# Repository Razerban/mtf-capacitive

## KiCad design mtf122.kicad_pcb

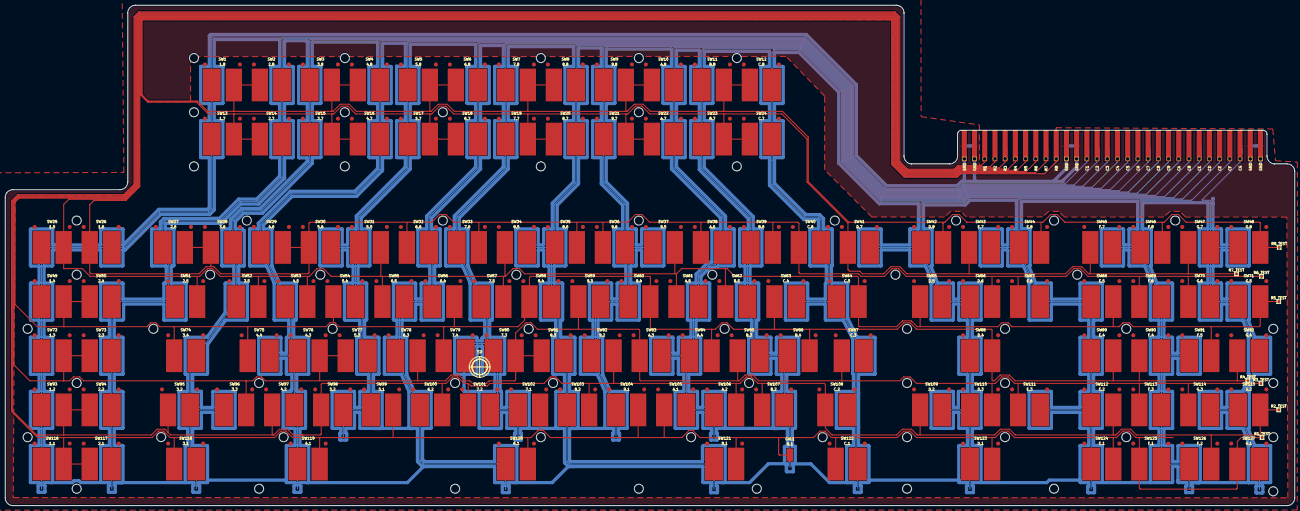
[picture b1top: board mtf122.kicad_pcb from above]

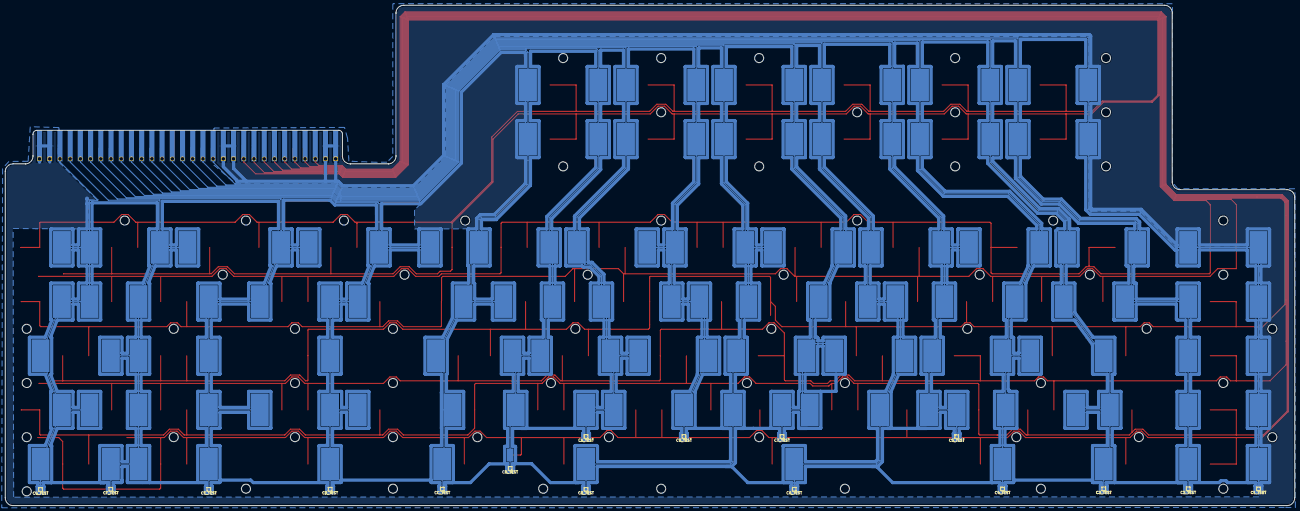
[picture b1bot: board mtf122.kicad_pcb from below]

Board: 2 copper layers, 500.0 x 194.0 mm, 153 parts (16 on the bottom side), 25 nets.

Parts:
C1_TEST, C2_TEST, C3_TEST, C4_TEST, C5_TEST, C6_TEST, C7_TEST, C8_TEST, C9_TEST: TestPoint_Pad_1.0x1.0mm
CAL1: B,1; CAL_CAP_IBM_F
CA_TEST: TestPoint_Pad_1.0x1.0mm
CB_TEST: TestPoint_Pad_1.0x1.0mm
CC_TEST: TestPoint_Pad_1.0x1.0mm
CD_TEST: TestPoint_Pad_1.0x1.0mm
CE_TEST: TestPoint_Pad_1.0x1.0mm
CF_TEST: TestPoint_Pad_1.0x1.0mm
CG_TEST: TestPoint_Pad_1.0x1.0mm
J1: CONN_CAP_IBM_F
R1_TEST, R2_TEST, R3_TEST, R4_TEST, R5_TEST, R6_TEST, R7_TEST, R8_TEST: TestPoint_Pad_1.0x1.0mm
SW1: 1,8; SW_CAP_IBM_F_ALT
SW2: 2,8; SW_CAP_IBM_F
SW3: 3,8; SW_CAP_IBM_F_ALT
SW4: 4,8; SW_CAP_IBM_F
SW5: 5,8; SW_CAP_IBM_F_ALT
SW6: 6,8; SW_CAP_IBM_F
SW7: 7,8; SW_CAP_IBM_F_ALT
SW8: 8,8; SW_CAP_IBM_F
SW9: 9,8; SW_CAP_IBM_F_ALT
SW10: A,8; SW_CAP_IBM_F
SW11: B,8; SW_CAP_IBM_F_ALT
SW12: C,8; SW_CAP_IBM_F
SW13: 1,7; SW_CAP_IBM_F_ALT
SW14: 2,7; SW_CAP_IBM_F
SW15: 3,7; SW_CAP_IBM_F_ALT
SW16: 4,7; SW_CAP_IBM_F
SW17: 5,7; SW_CAP_IBM_F_ALT
SW18: 6,7; SW_CAP_IBM_F
SW19: 7,7; SW_CAP_IBM_F_ALT
SW20: 8,7; SW_CAP_IBM_F
SW21: 9,7; SW_CAP_IBM_F_ALT
SW22: A,7; SW_CAP_IBM_F
SW23: B,7; SW_CAP_IBM_F_ALT
SW24: C,7; SW_CAP_IBM_F
SW25: 1,5; SW_CAP_IBM_F_ALT
SW26: 1,6; SW_CAP_IBM_F
SW27: 2,6; SW_CAP_IBM_F_ALT
SW28: 3,6; SW_CAP_IBM_F
SW29: 4,6; SW_CAP_IBM_F_ALT
SW30: 5,6; SW_CAP_IBM_F
SW31: 5,5; SW_CAP_IBM_F_ALT
SW32: 6,6; SW_CAP_IBM_F
SW33: 7,6; SW_CAP_IBM_F_ALT
SW34: 8,5; SW_CAP_IBM_F
SW35: 8,6; SW_CAP_IBM_F_ALT
SW36: 9,6; SW_CAP_IBM_F
SW37: 9,5; SW_CAP_IBM_F_ALT
SW38: A,6; SW_CAP_IBM_F
SW39: B,6; SW_CAP_IBM_F_ALT
SW40: C,6; SW_CAP_IBM_F
SW41: D,7; SW_CAP_IBM_F
SW42: D,8; SW_CAP_IBM_F_ALT
SW43: E,7; SW_CAP_IBM_F
SW44: E,8; SW_CAP_IBM_F_ALT
SW45: F,7; SW_CAP_IBM_F
SW46: F,8; SW_CAP_IBM_F_ALT
SW47: G,7; SW_CAP_IBM_F
SW48: G,8; SW_CAP_IBM_F_ALT
SW49: 1,4; SW_CAP_IBM_F_ALT
SW50: 2,4; SW_CAP_IBM_F
SW51: 2,5; SW_CAP_IBM_F_ALT
SW52: 3,5; SW_CAP_IBM_F_ALT
SW53: 4,5; SW_CAP_IBM_F_ALT
SW54: 5,4; SW_CAP_IBM_F
SW55: 6,5; SW_CAP_IBM_F
SW56: 6,4; SW_CAP_IBM_F_ALT
SW57: 7,5; SW_CAP_IBM_F_ALT
SW58: 8,4; SW_CAP_IBM_F
SW59: 9,3; SW_CAP_IBM_F
SW60: 9,4; SW_CAP_IBM_F_ALT
SW61: A,5; SW_CAP_IBM_F
SW62: B,5; SW_CAP_IBM_F
SW63: C,4; SW_CAP_IBM_F
SW64: C,5; SW_CAP_IBM_F_ALT
SW65: D,5; SW_CAP_IBM_F
SW66: D,6; SW_CAP_IBM_F_ALT
SW67: E,6; SW_CAP_IBM_F
SW68: E,5; SW_CAP_IBM_F_ALT
SW69: F,6; SW_CAP_IBM_F
SW70: G,6; SW_CAP_IBM_F
SW71: G,5; SW_CAP_IBM_F_ALT
SW72: 1,3; SW_CAP_IBM_F_ALT
SW73: 2,3; SW_CAP_IBM_F
SW74: 3,4; SW_CAP_IBM_F
SW75: 4,4; SW_CAP_IBM_F
SW76: 4,3; SW_CAP_IBM_F_ALT
SW77: 5,3; SW_CAP_IBM_F
SW78: 6,3; SW_CAP_IBM_F_ALT
SW79: 7,4; SW_CAP_IBM_F
SW80: 7,3; SW_CAP_IBM_F_ALT
SW81: 8,3; SW_CAP_IBM_F
SW82: 9,2; SW_CAP_IBM_F_ALT
SW83: A,3; SW_CAP_IBM_F
SW84: A,4; SW_CAP_IBM_F_ALT
SW85: B,3; SW_CAP_IBM_F
SW86: B,4; SW_CAP_IBM_F_ALT
SW87: C,3; SW_CAP_IBM_F
SW88: D,4; SW_CAP_IBM_F_ALT
SW89: E,4; SW_CAP_IBM_F_ALT
SW90: F,4; SW_CAP_IBM_F
SW91: F,5; SW_CAP_IBM_F_ALT
SW92: G,4; SW_CAP_IBM_F
SW93: 1,2; SW_CAP_IBM_F_ALT
SW94: 2,2; SW_CAP_IBM_F
SW95: 3,2; SW_CAP_IBM_F
SW96: 3,3; SW_CAP_IBM_F_ALT
SW97: 4,2; SW_CAP_IBM_F
SW98: 5,2; SW_CAP_IBM_F
SW99: 5,1; SW_CAP_IBM_F_ALT
SW100: 6,2; SW_CAP_IBM_F_ALT
SW101: 7,2; SW_CAP_IBM_F
SW102: 7,1; SW_CAP_IBM_F_ALT
SW103: 8,2; SW_CAP_IBM_F_ALT
SW104: 9,1; SW_CAP_IBM_F_ALT
SW105: A,1; SW_CAP_IBM_F
SW106: A,2; SW_CAP_IBM_F_ALT
SW107: B,2; SW_CAP_IBM_F
SW108: C,2; SW_CAP_IBM_F
SW109: D,2; SW_CAP_IBM_F
SW110: D,3; SW_CAP_IBM_F_ALT
SW111: E,3; SW_CAP_IBM_F
SW112: E,2; SW_CAP_IBM_F_ALT
SW113: F,3; SW_CAP_IBM_F
SW114: G,3; SW_CAP_IBM_F
SW115: G,2; SW_CAP_IBM_F_ALT
SW116: 1,1; SW_CAP_IBM_F_ALT
SW117: 2,1; SW_CAP_IBM_F
SW118: 3,1; SW_CAP_IBM_F
SW119: 4,1; SW_CAP_IBM_F_ALT
SW120: 6,1; SW_CAP_IBM_F_ALT
SW121: 8,1; SW_CAP_IBM_F_ALT
SW122: C,1; SW_CAP_IBM_F
SW123: D,1; SW_CAP_IBM_F_ALT
SW124: E,1; SW_CAP_IBM_F_ALT
SW125: F,1; SW_CAP_IBM_F
SW126: F,2; SW_CAP_IBM_F_ALT
SW127: G,1; SW_CAP_IBM_F

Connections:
COL_1: C1_TEST.9, J1.13, J1.43, J1.73, SW1.COL, SW13.COL, SW25.COL, SW26.COL, SW49.COL, SW72.COL, SW93.COL, SW116.COL
COL_2: C2_TEST.10, J1.14, J1.44, J1.74, SW2.COL, SW14.COL, SW27.COL, SW50.COL, SW51.COL, SW73.COL, SW94.COL, SW117.COL
COL_3: C3_TEST.11, J1.15, J1.45, J1.75, SW3.COL, SW15.COL, SW28.COL, SW52.COL, SW74.COL, SW95.COL, SW96.COL, SW118.COL
COL_4: C4_TEST.12, J1.16, J1.46, J1.76, SW4.COL, SW16.COL, SW29.COL, SW53.COL, SW75.COL, SW76.COL, SW97.COL, SW119.COL
COL_5: C5_TEST.13, J1.17, J1.47, J1.77, SW5.COL, SW17.COL, SW30.COL, SW31.COL, SW54.COL, SW77.COL, SW98.COL, SW99.COL
COL_6: C6_TEST.14, J1.18, J1.48, J1.78, SW6.COL, SW18.COL, SW32.COL, SW55.COL, SW56.COL, SW78.COL, SW100.COL, SW120.COL
COL_7: C7_TEST.15, J1.19, J1.49, J1.79, SW7.COL, SW19.COL, SW33.COL, SW57.COL, SW79.COL, SW80.COL, SW101.COL, SW102.COL
COL_8: C8_TEST.16, J1.20, J1.50, J1.80, SW8.COL, SW20.COL, SW34.COL, SW35.COL, SW58.COL, SW81.COL, SW103.COL, SW121.COL
COL_9: C9_TEST.17, J1.21, J1.51, J1.81, SW9.COL, SW21.COL, SW36.COL, SW37.COL, SW59.COL, SW60.COL, SW82.COL, SW104.COL
COL_A: CA_TEST.18, J1.22, J1.52, J1.82, SW10.COL, SW22.COL, SW38.COL, SW61.COL, SW83.COL, SW84.COL, SW105.COL, SW106.COL
COL_B: CAL1.COL, CB_TEST.19, J1.23, J1.53, J1.83, SW11.COL, SW23.COL, SW39.COL, SW62.COL, SW85.COL, SW86.COL, SW107.COL
COL_C: CC_TEST.20, J1.24, J1.54, J1.84, SW12.COL, SW24.COL, SW40.COL, SW63.COL, SW64.COL, SW87.COL, SW108.COL, SW122.COL
COL_D: CD_TEST.21, J1.25, J1.55, J1.85, SW41.COL, SW42.COL, SW65.COL, SW66.COL, SW88.COL, SW109.COL, SW110.COL, SW123.COL
COL_E: CE_TEST.21, J1.26, J1.56, J1.86, SW43.COL, SW44.COL, SW67.COL, SW68.COL, SW89.COL, SW111.COL, SW112.COL, SW124.COL
COL_F: CF_TEST.22, J1.27, J1.57, J1.87, SW45.COL, SW46.COL, SW69.COL, SW90.COL, SW91.COL, SW113.COL, SW125.COL, SW126.COL
COL_G: CG_TEST.23, J1.28, J1.58, J1.88, SW47.COL, SW48.COL, SW70.COL, SW71.COL, SW92.COL, SW114.COL, SW115.COL, SW127.COL
GND: J1.1, J1.2, J1.11, J1.12, J1.29, J1.30, J1.31, J1.32, J1.41, J1.42, J1.59, J1.60, J1.61, J1.62, J1.71, J1.72, J1.89, J1.90
ROW_1: CAL1.ROW, J1.3, J1.33, R1_TEST.1, SW99.ROW, SW102.ROW, SW104.ROW, SW105.ROW, SW116.ROW, SW117.ROW, SW118.ROW, SW119.ROW, SW120.ROW, SW121.ROW, SW122.ROW, SW123.ROW, SW124.ROW, SW125.ROW, SW127.ROW
ROW_2: J1.4, J1.34, R2_TEST.2, SW82.ROW, SW93.ROW, SW94.ROW, SW95.ROW, SW97.ROW, SW98.ROW, SW100.ROW, SW101.ROW, SW103.ROW, SW106.ROW, SW107.ROW, SW108.ROW, SW109.ROW, SW112.ROW, SW115.ROW, SW126.ROW
ROW_3: J1.5, J1.35, R3_TEST.3, SW59.ROW, SW72.ROW, SW73.ROW, SW76.ROW, SW77.ROW, SW78.ROW, SW80.ROW, SW81.ROW, SW83.ROW, SW85.ROW, SW87.ROW, SW96.ROW, SW110.ROW, SW111.ROW, SW113.ROW, SW114.ROW
ROW_4: J1.6, J1.36, R4_TEST.4, SW49.ROW, SW50.ROW, SW54.ROW, SW56.ROW, SW58.ROW, SW60.ROW, SW63.ROW, SW74.ROW, SW75.ROW, SW79.ROW, SW84.ROW, SW86.ROW, SW88.ROW, SW89.ROW, SW90.ROW, SW92.ROW
ROW_5: J1.7, J1.37, R5_TEST.5, SW25.ROW, SW31.ROW, SW34.ROW, SW37.ROW, SW51.ROW, SW52.ROW, SW53.ROW, SW55.ROW, SW57.ROW, SW61.ROW, SW62.ROW, SW64.ROW, SW65.ROW, SW68.ROW, SW71.ROW, SW91.ROW
ROW_6: J1.8, J1.38, R6_TEST.6, SW26.ROW, SW27.ROW, SW28.ROW, SW29.ROW, SW30.ROW, SW32.ROW, SW33.ROW, SW35.ROW, SW36.ROW, SW38.ROW, SW39.ROW, SW40.ROW, SW66.ROW, SW67.ROW, SW69.ROW, SW70.ROW
ROW_7: J1.9, J1.39, R7_TEST.7, SW13.ROW, SW14.ROW, SW15.ROW, SW16.ROW, SW17.ROW, SW18.ROW, SW19.ROW, SW20.ROW, SW21.ROW, SW22.ROW, SW23.ROW, SW24.ROW, SW41.ROW, SW43.ROW, SW45.ROW, SW47.ROW
ROW_8: J1.10, J1.40, R8_TEST.8, SW1.ROW, SW2.ROW, SW3.ROW, SW4.ROW, SW5.ROW, SW6.ROW, SW7.ROW, SW8.ROW, SW9.ROW, SW10.ROW, SW11.ROW, SW12.ROW, SW42.ROW, SW44.ROW, SW46.ROW, SW48.ROW

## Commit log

2021-01-23 Removed drawings from back and front silkscreen
2021-01-24 Updated the PCB edge lines with the old style M122 barrel plate design
2021-01-24 Changed the controller pins location and rerouted the connections on B.Cu
2021-01-24 Changed the controller pins location and rerouted the connections on the F.Cu
2021-01-25 Changed the PCB edges and rerouter the row connections
2021-01-25 Added Copper fill areas
2021-01-25 Added an extra copper fill area and resized the others
2021-01-25 Removed unnecessary solder mask
2021-01-26 Removed redundant edge
2021-01-26 Updated traces and copper fill areas
2021-01-26 Added extra connection to be compliant with IBM rule: all rows and columns must cross exactly the same number of times
2021-01-26 Made the PCB corners rounded
2021-01-28 Added pins for card edge connector
2021-01-29 Update card edge reader footprint and adjusted / rerouted the connections
2021-01-29 Removed the extra non-connected pads
2021-01-29 Added additionnal copper layer on the edges of the PCB
2021-01-29 Added a new footprint for the card edge connector design
2021-01-30 Placed some test points to check continuity of rows and columns
